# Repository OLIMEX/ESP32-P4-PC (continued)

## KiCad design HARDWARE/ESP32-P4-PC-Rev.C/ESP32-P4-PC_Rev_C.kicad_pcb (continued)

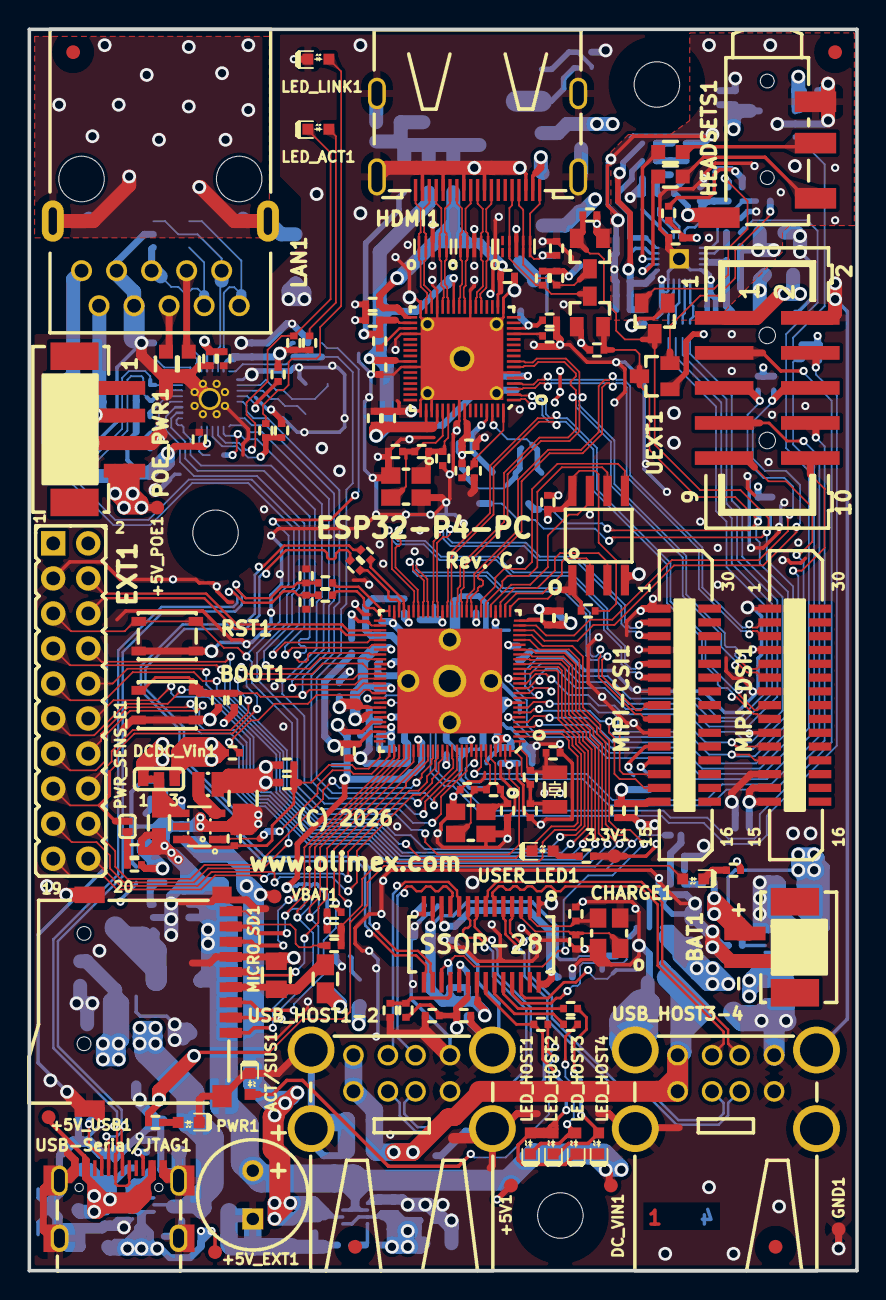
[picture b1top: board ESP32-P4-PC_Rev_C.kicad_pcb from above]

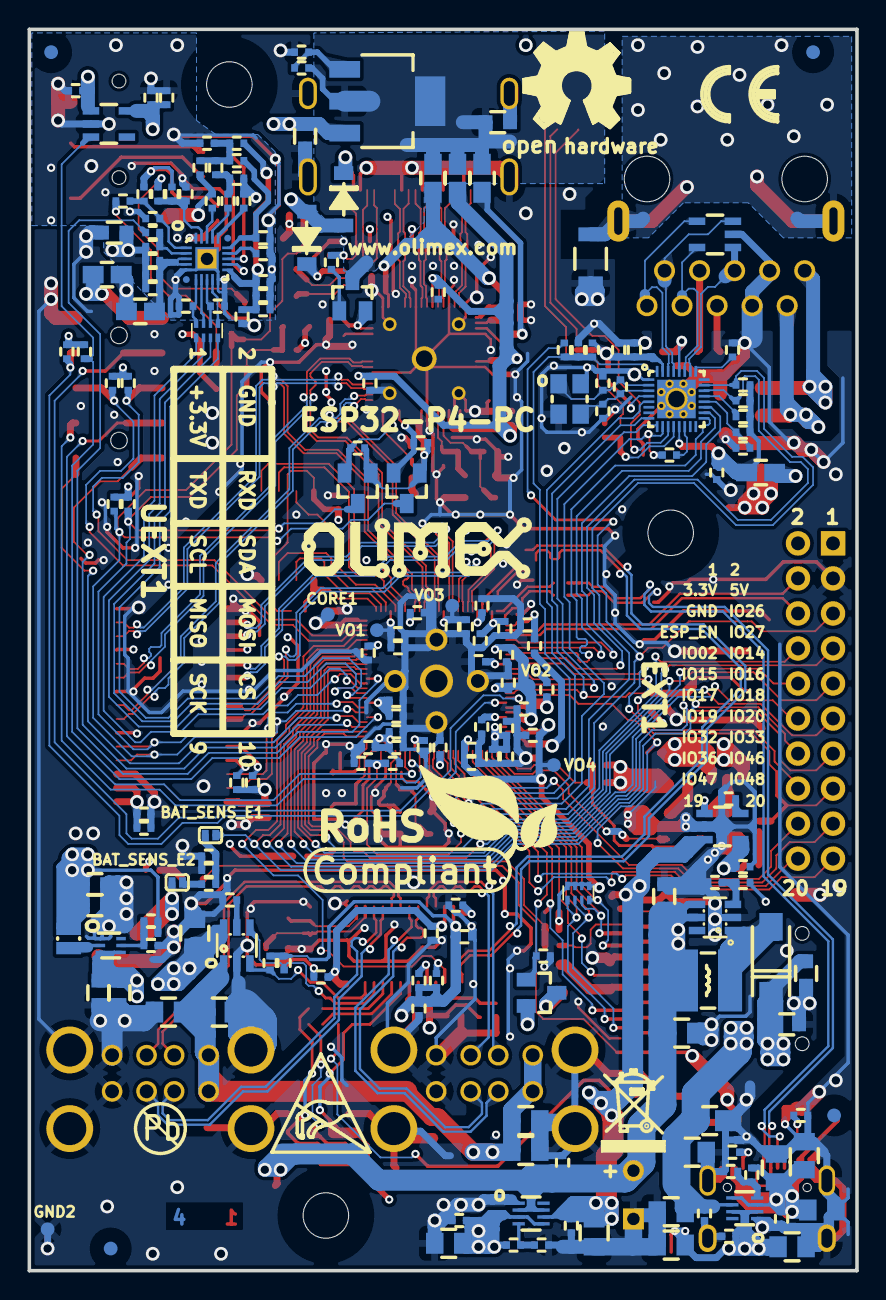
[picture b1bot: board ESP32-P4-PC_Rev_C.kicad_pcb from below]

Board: 4 copper layers, 60.0 x 90.0 mm, 344 parts (204 on the bottom side), 223 nets.

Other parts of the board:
Logo_OLIMEX_TB: Logo_OLIMEX_TB
Sign_Antistatic: Sign_Antistatic
Sign_CE: CE_Sign
Sign_OSHW_8x8: Sign_OSHW_8x8
Sign_PB-Free: Sign_PB-Free
Sign_RecycleBin_1: Sign_RecycleBin_1
Sign_RoHS_1: Sign_RoHS_1

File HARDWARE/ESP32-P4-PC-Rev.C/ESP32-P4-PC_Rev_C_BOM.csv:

Quantity,Value,Footprint,Reference
2,LED/RED/0603,LED_0603_KA,"ACT/SUS1, PWR1"
1,PH2.0-2AT,PH2.0-2AT(BAT),BAT1
2,YTS-A016-X,YTS-A016-X,"BOOT1, RST1"
4,22pF/50V/5%/C0G/C0402,C_0402_5MIL_DWS,"C1, C2, C44, C45"
15,10uF/6.3V/20%/X5R/C0402,C_0402_5MIL_DWS,"C3, C6, C18, C20, C22, C29, C41, C50, C56, C67, C68, C70, C76, C82, C99"
46,100nF/10V/20%/X5R/C0402,C_0402_5MIL_DWS,"C4, C5, C7, C9, C11, C12, C19, C21, C23, C30, C31, C32, C38, C40, C42, C43, C46, C47, C49, C51, C52, C53, C54, C57, C69, C71, C85, C87, C91, C94, C95, C96, C101, C105, C106, C107, C108, C109, C111, C112, C115, C119, C120, C121, C128, C131"
16,1uF/6.3V/10%/X5R/C0402,C_0402_5MIL_DWS,"C8, C10, C36, C39, C48, C55, C58, C61, C84, C86, C88, C97, C98, C100, C104, C126"
1,4.7uF/X5R/20%/10V/C0402,C_0402_5MIL_DWS,C13
12,47uF/6.3V/20%/X5R/C0805,C_0805_5MIL_DWS,"C14, C65, C74, C92, C93, C118, C129, C130, C132, C133, C134, C136"
2,100nF/50V/20%/Y5V/C0603,C_0603_5MIL_DWS,"C15, C16"
1,1nF/2000V/10%/X7R/C1206,C_1206_5MIL_DWS_ISO,C17
7,27pF/50V/5%/C0G/C0402,C_0402_5MIL_DWS,"C24, C25, C79, C80, C81, C113, C114"
9,22uF/6.3V/20%/X5R/C0603,C_0603_5MIL_DWS,"C35, C37, C63, C66, C75, C102, C103, C123, C124"
2,20pF/50V/5%/NP0/C0402,C_0402_5MIL_DWS,"C77, C78"
1,2.2nF/50V/10%/X7R/C0402,C_0402_5MIL_DWS,C110
1,1000uF/10V/20%,CPOL-RM3.5mm_8.0x11.5mm_PTH,C117
2,LED/Yellow/0603,LED_0603_KA,"CHARGE1, LED_ACT1"
2,1N5819S4(SOD123),SOD-123_1C-2A_KA,"D2, D3"
1,1N5822/SS34/SMA,SMA-KA,D4
1,IRLML6402TRPBF-JSM(SOT-23),SOT23,FET1
6,BSS138(SOT-23),SOT23,"FET3, FET4, FET5, FET6, FET7, FET8"
1,HDMI-SWM-19,HDMI-SWM-19_Paste,HDMI1
1,PJ-320D,PJ-320D,HEADSETS1
6,600OHM/2A/UPZ2012E-601-2R0TF/0805,L_0805_5MIL_DWS,"L1, L2, L5, L6, L7, L8"
1,1.0uH/4.2A/DCR=35mR/20%/2.00x1.60x1.00mm/L2016(PIM201610-1R0MTS00),L_2016_MM,L3
1,2.2uH/2.1A/PIM201610-2R2MTS00,L_2016_MM,L4
1,4.7uH/2.20A/DCR=70mR/20%/CD43(SPH4018H4R7MT),CD42(43),L11
1,RJP-003TC1(LPJ4112CNL),RJP-003TC1(LPJ4112CNL),LAN1
6,LED/GREEN/0603,LED_0603_KA,"LED_HOST1, LED_HOST2, LED_HOST3, LED_HOST4, LED_LINK1, USER_LED1"
1,TFC-WPAPR-08-LF,TFC-WPAPR-08,MICRO_SD1
2,FPA-VZA2-15-LF,TE_1-1734248-5,"MIPI-CSI1, MIPI-DSI1"
1,PH2.0-4AT,PH2.0-4PLB,POE_PWR1
1,Q32.768kHz/12.5pF/2P/SMD1206,CM7V-T1A(Crystal_Package-1206_3.20x1.50x0.65mm),Q1
2,Q25MHz/18pF/30ppm/4P/3.2x2.5mm(ABM8-25.000MHZ-D2Y-T),TSX-3.2x2.5mm_GND(3),"Q2, Q6"
1,Q40.000MHz/12pF/10ppm/4P/3.2x2.5x0.70mm(Harmony_Electronics_CORP./HSX321S),TSX-3.2x2.5mm_GND(3),Q3
1,Q12MHz/18pF/30ppm/4P/3.2x2.5mm(ABM8-12.000MHZ-D2Y-T),TSX-3.2x2.5mm_GND(3),Q4
1,BC817-40,SOT23,Q5
2,4.02k/1%/R0402,R_0402_5MIL_DWS,"R1, R2"
17,10k/R0402,R_0402_5MIL_DWS,"R3, R27, R41, R42, R43, R48, R54, R55, R64, R66, R67, R68, R70, R83, R85, R86, R102"
18,2.2k/R0402,R_0402_5MIL_DWS,"R4, R8, R9, R39, R56, R57, R61, R62, R72, R73, R74, R80, R82, R84, R88, R91, R92, R93"
2,5.1k/1%/R0402,R_0402_5MIL_DWS,"R5, R6"
10,4.7k/R0402,R_0402_5MIL_DWS,"R7, R10, R11, R12, R21, R22, R33, R37, R49, R69"
1,10M/R0402,R_0402_5MIL_DWS,R13
6,22R/R0402,R_0402_5MIL_DWS,"R14, R15, R16, R25, R26, R38"
1,6.19k/1%/R0402,R_0402_5MIL_DWS,R17
2,24.9k/1%/R0402,R_0402_5MIL_DWS,"R24, R105"
1,0R/R0603,R_0603_5MIL_DWS,R31
2,1.5k/R0402,R_0402_5MIL_DWS,"R34, R35"
1,220k/R0402,R_0402_5MIL_DWS,R36
1,30.1k/1%/R0402,R_0402_5MIL_DWS,R44
1,6.49k/1%/R0402,R_0402_5MIL_DWS,R45
2,10.5k/1%/R0402,R_0402_5MIL_DWS,"R46, R47"
1,110R/1%/R0402,R_0402_5MIL_DWS,R50
1,49.9k/1%/R0402,R_0402_5MIL_DWS,R51
1,240R/1%/R0402,R_0402_5MIL_DWS,R52
1,2.7k/1%/R0402,R_0402_5MIL_DWS,R53
3,33R/R0402,R_0402_5MIL_DWS,"R58, R59, R60"
3,100k/R0402,R_0402_5MIL_DWS,"R65, R71, R75"
1,6.04k/1%/R0402,R_0402_5MIL_DWS,R76
1,10R/R0402,R_0402_5MIL_DWS,R77
1,200R/R0402,R_0402_5MIL_DWS,R79
1,1M/R0402,R_0402_5MIL_DWS,R87
2,6.81k/1%/R0402,R_0402_5MIL_DWS,"R89, R103"
3,470k/R0402,R_0402_5MIL_DWS,"R90, R94, R96"
1,8.25k/1%/R0402,R_0402_5MIL_DWS,R95
1,1.05k/1%/R0402,R_0402_5MIL_DWS,R98
1,RMAT_(4x0402)_4.7k,RA0805_(4X0402)_xx_BIGGEROUTPADS,RM1
1,RA0805_(4X0402)_33R,RA0805_(4X0402)_xx_BIGGEROUTPADS,RM2
1,ESDS314DBVR(SOT-23-5),SOT-23-5,TVS1
1,ESP32-P4NRWxx(QFN104),QFN104_10mm×10mm_Pitch_0.35mm,U1
1,IP101GRR(32-PIN_QFN),QFN32_EP(33)_4.00x4.00x0.80mm_Pitch_0.40mm,U2
1,W25Q128JVSIQ(16MB),SO-8_208mil,U3
1,TPS62A02ADRLR(SOT-563-6),SOT-563-6,U4
1,TLV62569PDDCR(SOT23-6),SOT23-6,U5
1,CH217K(SOT23-6L),SOT23-6,U6
1,FE1.1s(SSOP-28),SSOP28_10x4mm_Pitch_0.64mm,U7
1,ES8311(QFN-20),QFN-20_EP(21)_3x3x0.6mm_Pitch_0.4mm,U8
1,LT8912B(QFN64),QFN64_7.5x7.5mm_Pitch_0.4mm,U12
2,TPS2116,SOT-5X3,"U13, U16"
1,MT3608(SOT23-6),SOT23-6,U14
1,TP4054-42-SOT25-R(SOT23-5),SOT-23-5,U15
1,P-B-V-10-LF,GBH-254-SMT-10,UEXT1
1,USB-C-16P-F(A40-00119-A52-12),USB2.0_TYPE-C(A40-00119-A52-12)_Paste,USB-Serial/JTAG1
2,USBB1-FRWH-4A(USB-Ax2),USB_TWO_LEVEL,"USB_HOST1-2, USB_HOST3-4"
1,LD1117AG-AD-AA3-A-R,SOT223,VR1
1,AP1231-3.3V(SOT23-5),SOT-23-5,VR2

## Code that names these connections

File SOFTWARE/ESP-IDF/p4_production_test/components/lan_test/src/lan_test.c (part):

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/* ---- Kconfig ---- */
#define PHY_ADDR         CONFIG_LAN_TEST_PHY_ADDR
#define PHY_RST_GPIO     CONFIG_LAN_TEST_PHY_RST_GPIO
#define MDC_GPIO         CONFIG_LAN_TEST_MDC_GPIO
#define MDIO_GPIO        CONFIG_LAN_TEST_MDIO_GPIO
#define RMII_CLK_GPIO    CONFIG_LAN_TEST_RMII_CLK_IN_GPIO

/* ---- Events ---- */
#define BIT_LINK_UP  (1U << 0)
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    eth_esp32_emac_config_t emac_cfg = ETH_ESP32_EMAC_DEFAULT_CONFIG();

    // ESP32-P4 naming: mdc_num/mdio_num
    emac_cfg.smi_gpio.mdc_num  = MDC_GPIO;
    emac_cfg.smi_gpio.mdio_num = MDIO_GPIO;

    emac_cfg.interface = EMAC_DATA_INTERFACE_RMII;

    // External 50 MHz REF_CLK input
    emac_cfg.clock_config.rmii.clock_mode = EMAC_CLK_EXT_IN;
    emac_cfg.clock_config.rmii.clock_gpio = RMII_CLK_GPIO;

    s_mac = esp_eth_mac_new_esp32(&emac_cfg, &mac_cfg);
    if (!s_mac) { lan_test_deinit(); return ESP_ERR_NO_MEM; }
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
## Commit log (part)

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2026-02-17 initial upload
2026-02-17 add user manual
2026-03-02 ESP-IDF production test
    New demo
